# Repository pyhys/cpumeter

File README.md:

# CPU meter from an old Desynn avionics instrument

Show the min and max utilisation of the CPU cores in your laptop. Connect via USB!

https://github.com/pyhys/cpumeter/assets/1586574/e618666e-b38f-4fe2-83e1-2e9af869577b

Original indicator use in for example Hawker Hunter
---------------------------------------------------
Several variants with different labels

https://en.wikipedia.org/wiki/Hawker_Hunter

External view
https://www.jetphotos.com/photo/10868031

Cockpit photo
https://www.jetphotos.com/photo/9365230

Circuit design
--------------
Six voltages 0-24 V

DAC for analog outputs variant?

Amplifier 0-2 V to 0-24 V variant?

Power amplifiers (voltage followers) transistors ?

Timer circuit monostable 74LS123

USB-to-SPI

FT232H
https://ftdichip.com/products/ft232hq/

Adafruit Breakout board
https://www.adafruit.com/product/2264

Here is the resulting schematics:

PCB design
----------
Kicad https://www.kicad.org/

Software
--------
Written in Python

Autostart with udev and systemd

Installation
------------

Install the Python dependencies so they are available for the root user.

```
sudo mkdir /opt/cpumeter
sudo cp src/cpumeter.sh /usr/local/bin/cpumeter
sudo cp src/cpumeter_daemon.py /opt/cpumeter/
sudo cp src/95-cpumeter.rules /etc/udev/rules.d/
sudo cp src/cpumeter.service /etc/systemd/system/
```

udev
----
```
sudo udevadm control --reload
udevadm trigger
udevadm monitor
udevadm monitor --property
udevadm monitor --env
```

Start or stop the daemon
------------------------
```
sudo systemctl daemon-reload
sudo systemctl restart cpumeter.service
sudo systemctl stop cpumeter.service
```

Show log file
-------------
```
sudo systemctl status cpumeter.service
journalctl -u cpumeter.service
journalctl -u cpumeter.service -f
```

Indicator working principle
---------------------------
Smiths desynn

See http://avionicengineer.blogspot.com/2011/03/synchronous-data-transmission.html

Discussion on https://www.youtube.com/watch?v=2iqJ6352u74

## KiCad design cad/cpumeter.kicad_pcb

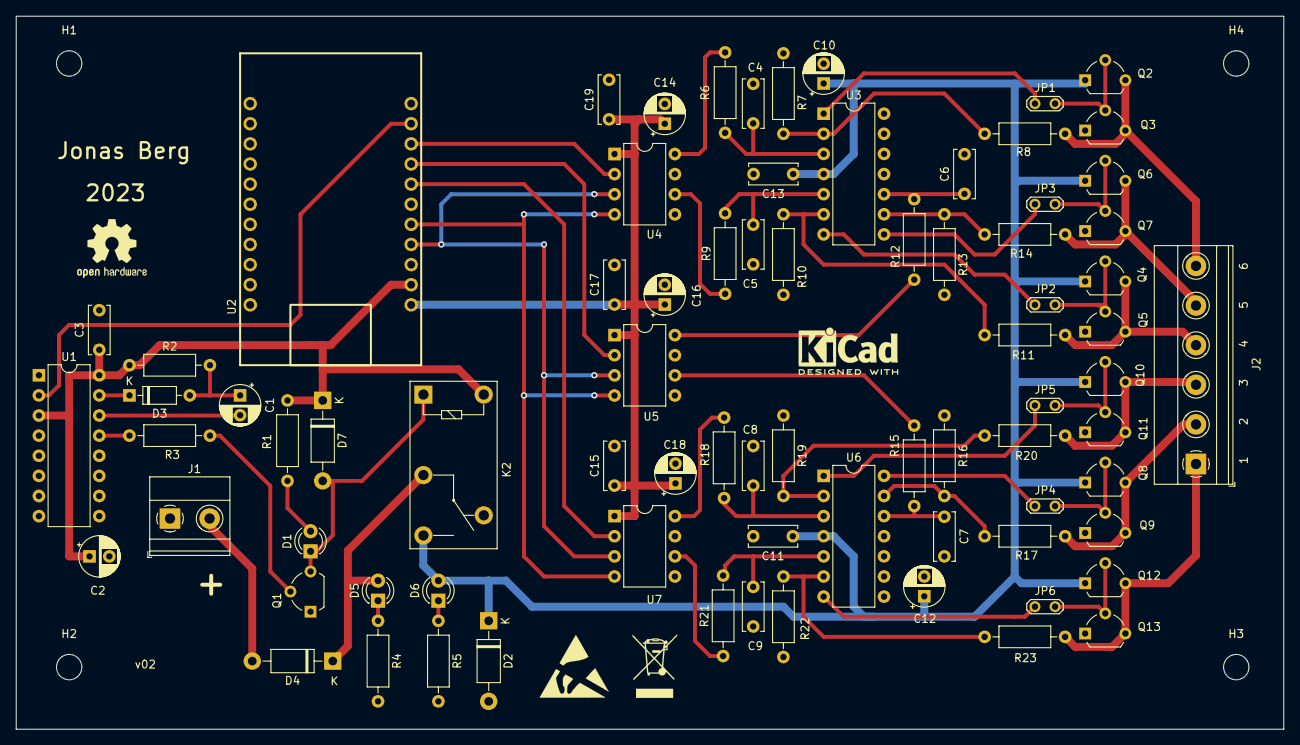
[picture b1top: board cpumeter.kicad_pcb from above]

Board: 2 copper layers, 160.0 x 90.0 mm, 82 parts (0 on the bottom side), 57 nets.

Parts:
C1: 25uF; CP_Radial_D5.0mm_P2.50mm
C2, C14, C16, C18: 10uF; CP_Radial_D5.0mm_P2.50mm
C3, C4, C5, C6, C7, C8, C9, C15, C17, C19: 100nF; C_Disc_D6.0mm_W2.5mm_P5.00mm
C10, C12: 16uF; CP_Radial_D5.0mm_P2.50mm
C11, C13: 160nF; C_Disc_D6.0mm_W2.5mm_P5.00mm
D1: Yellow; LED_D3.0mm
D2, D4, D7: 1N4003; D_DO-41_SOD81_P10.16mm_Horizontal
D3: 1N4148; D_DO-35_SOD27_P7.62mm_Horizontal
D5, D6: Green; LED_D3.0mm
H1, H2, H3, H4: MountingHole; MountingHole_3.2mm_M3
J1: Screw_Terminal_01x02; TerminalBlock_Phoenix_MKDS-1,5-2_1x02_P5.00mm_Horizontal
J2: Screw_Terminal_01x06; TerminalBlock_Phoenix_MKDS-1,5-6_1x06_P5.00mm_Horizontal
JP1, JP2, JP3, JP4, JP5, JP6: Jumper_2_Bridged; TestPoint_2Pads_Pitch2.54mm_Drill0.8mm
K2: G5Q-1; Relay_SPDT_Omron-G5Q-1
Q1: 2N7000; TO-92L_Wide
Q2, Q4, Q6, Q8, Q10, Q12: BC547; TO-92L_Wide
Q3, Q5, Q7, Q9, Q11, Q13: BC557; TO-92L_Wide
R1: 560; R_Axial_DIN0207_L6.3mm_D2.5mm_P10.16mm_Horizontal
R2: 100k; R_Axial_DIN0207_L6.3mm_D2.5mm_P10.16mm_Horizontal
R3, R6, R8, R9, R11, R12, R14, R15, R17, R18, R20, R21, R23: 10k; R_Axial_DIN0207_L6.3mm_D2.5mm_P10.16mm_Horizontal
R4, R5: 3k3; R_Axial_DIN0207_L6.3mm_D2.5mm_P10.16mm_Horizontal
R7, R10, R13, R16, R19, R22: 1k; R_Axial_DIN0207_L6.3mm_D2.5mm_P10.16mm_Horizontal
U1: 74LS123; DIP-16_W7.62mm
U2: ft232h_footprint
U3, U6: LM324; DIP-14_W7.62mm
U4, U5, U7: MCP4812; DIP-8_W7.62mm

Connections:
+3.3V: C14.1, C15.1, C16.1, C17.1, C18.1, C19.1, U2.1 (3V), U4.1 (Vdd), U5.1 (Vdd), U7.1 (Vdd)
+5V: C2.1, C3.1, D7.1 (K), K2.5, R1.1, R2.1, U1.3 (Clr), U1.16 (VCC), U2.2 (5V)
+24V: C10.1, C11.1, C12.1, C13.1, D2.1 (K), D6.2 (A), K2.3, Q2.1 (C), Q4.1 (C), Q6.1 (C), Q8.1 (C), Q10.1 (C), Q12.1 (C), U3.4 (V+), U6.4 (V+)
+VDC: D4.1 (K), D5.2 (A), K2.2
/Analog/CS0: U2.7 (D3_CS0), U7.2 (~CS)
/Analog/CS1: U2.8 (D4_CS1), U5.2 (~CS)
/Analog/CS2: U2.9 (D5_CS2), U4.2 (~CS)
/Analog/MOSI: U2.5 (D1_MOSI), U4.4 (SDI), U5.4 (SDI), U7.4 (SDI)
/Analog/SCLK: U2.4 (D0_SCLK), U4.3 (SCK), U5.3 (SCK), U7.3 (SCK)
/Analog/Vout1: J2.6, Q2.3 (E), Q3.3 (E), R8.2
/Analog/Vout2: J2.4, Q4.3 (E), Q5.3 (E), R11.2
/Analog/Vout3: J2.5, Q6.3 (E), Q7.3 (E), R14.2
/Analog/Vout4: J2.2, Q8.3 (E), Q9.3 (E), R17.2
/Analog/Vout5: J2.3, Q10.3 (E), Q11.3 (E), R20.2
/Analog/Vout6: J2.1, Q12.3 (E), Q13.3 (E), R23.2
GND: C2.2, C3.2, C4.2, C5.2, C6.2, C7.2, C8.2, C9.2, C10.2, C11.2, C12.2, C13.2, C14.2, C15.2, C16.2, C17.2, C18.2, C19.2, D2.2 (A), J1.1, Q1.1 (S), Q3.1 (C), Q5.1 (C), Q7.1 (C), Q9.1 (C), Q11.1 (C), Q13.1 (C), R4.2, R5.2, R7.1, R10.1, R13.1, R16.1, R19.1, R22.1, U1.1 (A), U1.8 (GND), U2.3 (GND1), U2.22 (GND2), U3.11 (V-), U4.5 (~LDAC), U4.7 (Vss), U5.5 (~LDAC), U5.7 (Vss), U6.11 (V-), U7.5 (~LDAC), U7.7 (Vss)
unnamed: D1.2 (A), R1.2
unnamed: D1.1 (K), D7.2 (A), K2.1, Q1.3 (D)
unnamed: C1.1, D3.2 (A), R2.2
unnamed: D3.1 (K), U1.15 (RCext)
unnamed: D4.2 (A), J1.2
unnamed: D5.1 (K), R4.1
unnamed: D6.1 (K), R5.1
unnamed: JP1.1 (A), U3.1
unnamed: JP1.2 (B), Q2.2 (B), Q3.2 (B)
unnamed: JP2.1 (A), U3.7
unnamed: JP2.2 (B), Q4.2 (B), Q5.2 (B)
unnamed: JP3.1 (A), U3.8
unnamed: JP3.2 (B), Q6.2 (B), Q7.2 (B)
unnamed: JP4.1 (A), U6.14
unnamed: JP4.2 (B), Q8.2 (B), Q9.2 (B)
unnamed: JP5.1 (A), U6.1
unnamed: JP5.2 (B), Q10.2 (B), Q11.2 (B)
unnamed: JP6.1 (A), U6.7
unnamed: JP6.2 (B), Q12.2 (B), Q13.2 (B)
unnamed: Q1.2 (G), R3.2
unnamed: U1.2 (B), U2.10 (D6_digout)
unnamed: C1.2, U1.14 (Cext)
unnamed: R3.1, U1.13 (Q)
unnamed: C4.1, R6.2, U3.3 (+)
unnamed: R7.2, R8.1, U3.2 (-)
unnamed: C5.1, R9.2, U3.5 (+)
unnamed: R10.2, R11.1, U3.6 (-)
unnamed: C6.1, R12.2, U3.10 (+)
unnamed: R13.2, R14.1, U3.9 (-)
unnamed: R6.1, U4.8 (VA)
unnamed: R9.1, U4.6 (VB)
unnamed: R12.1, U5.8 (VA)
unnamed: R15.1, U5.6 (VB)
unnamed: C8.1, R18.2, U6.3 (+)
unnamed: R19.2, R20.1, U6.2 (-)
unnamed: C9.1, R21.2, U6.5 (+)
unnamed: R22.2, R23.1, U6.6 (-)
unnamed: C7.1, R15.2, U6.12 (+)
unnamed: R16.2, R17.1, U6.13 (-)
unnamed: R18.1, U7.8 (VA)
unnamed: R21.1, U7.6 (VB)

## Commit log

2023-10-16 Update README.md
    Added video
2023-10-16 Update README.md
    More video experiments

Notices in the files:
cad/cpumeter.kicad_pcb:
License CC BY 4.0
